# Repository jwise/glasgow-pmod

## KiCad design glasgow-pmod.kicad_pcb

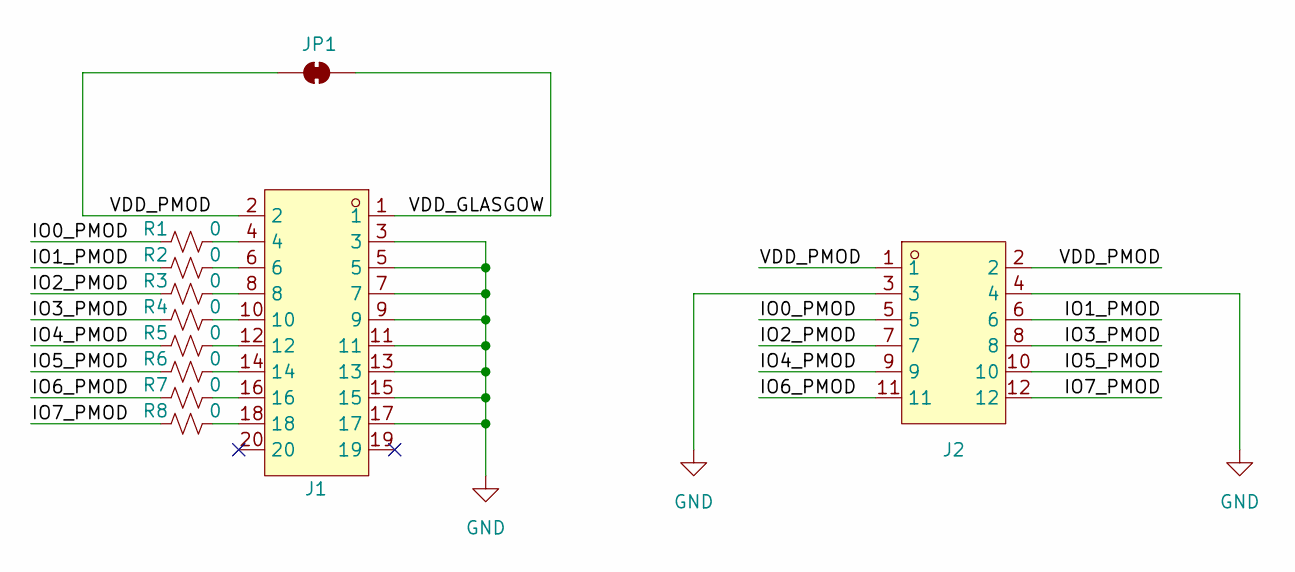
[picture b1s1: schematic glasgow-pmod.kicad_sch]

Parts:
J1: HDR-TH_20P-P2.54-V-F-R2-C10-S2.54; LCSC Part C2897411
J2: PM254-2-06-W-8.5; HDR-TH_12P-P2.54-H-F-R2-C6-W8.5; LCSC Part C2897426
JP1: SolderJumper_2_Bridged; SolderJumper-2_P1.3mm_Bridged_RoundedPad1.0x1.5mm
R1, R2, R3, R4, R5, R6, R7, R8: 0; R_0603_1608Metric; LCSC C21189

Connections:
/IO0_PMOD: J2.5, R1.1
/IO1_PMOD: J2.6, R2.1
/IO2_PMOD: J2.7, R3.1
/IO3_PMOD: J2.8, R4.1
/IO4_PMOD: J2.9, R5.1
/IO5_PMOD: J2.10, R6.1
/IO6_PMOD: J2.11, R7.1
/IO7_PMOD: J2.12, R8.1
/VDD_GLASGOW: J1.1, JP1.2 (B)
/VDD_PMOD: J1.2, J2.1, J2.2, JP1.1 (A)
GND: J1.3, J1.5, J1.7, J1.9, J1.11, J1.13, J1.15, J1.17, J2.3, J2.4
unnamed: J1.4, R1.2
unnamed: J1.6, R2.2
unnamed: J1.8, R3.2
unnamed: J1.10, R4.2
unnamed: J1.12, R5.2
unnamed: J1.14, R6.2
unnamed: J1.16, R7.2
unnamed: J1.18, R8.2

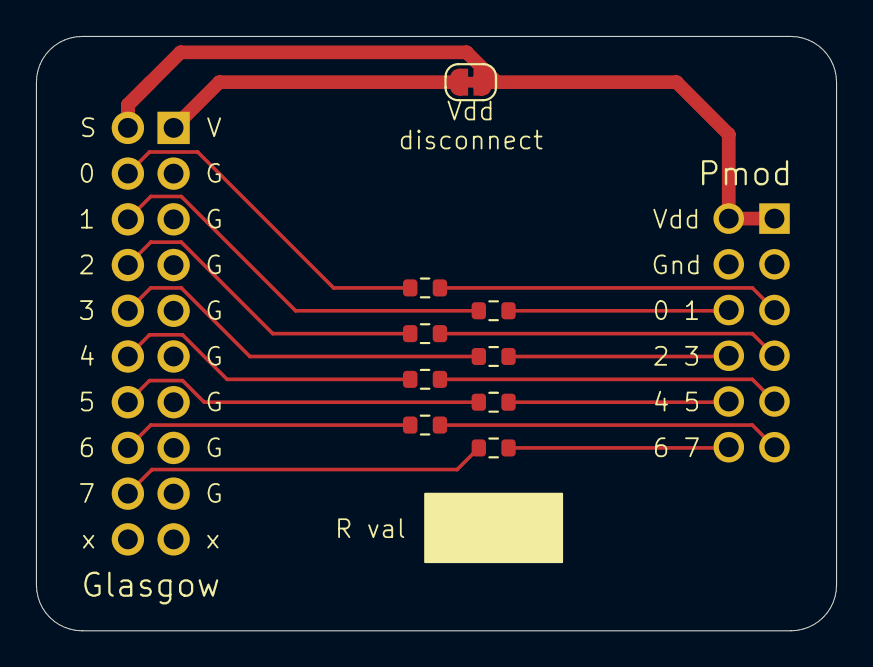
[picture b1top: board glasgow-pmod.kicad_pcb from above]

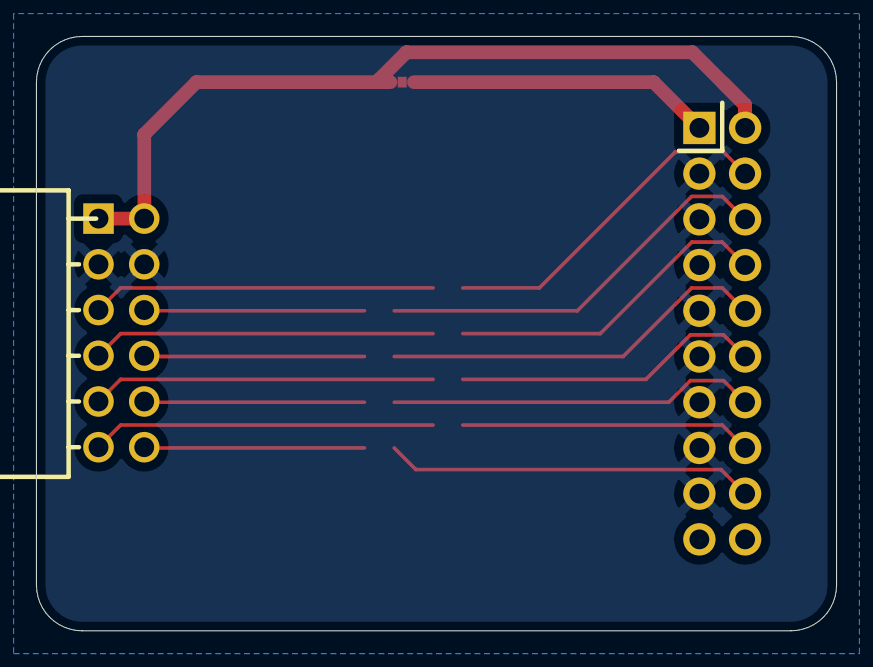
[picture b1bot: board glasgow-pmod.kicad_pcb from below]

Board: 2 copper layers, 44.4 x 33.0 mm, 11 parts (2 on the bottom side), 19 nets.

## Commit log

2024-06-30 glasgow pmod adapter A01
